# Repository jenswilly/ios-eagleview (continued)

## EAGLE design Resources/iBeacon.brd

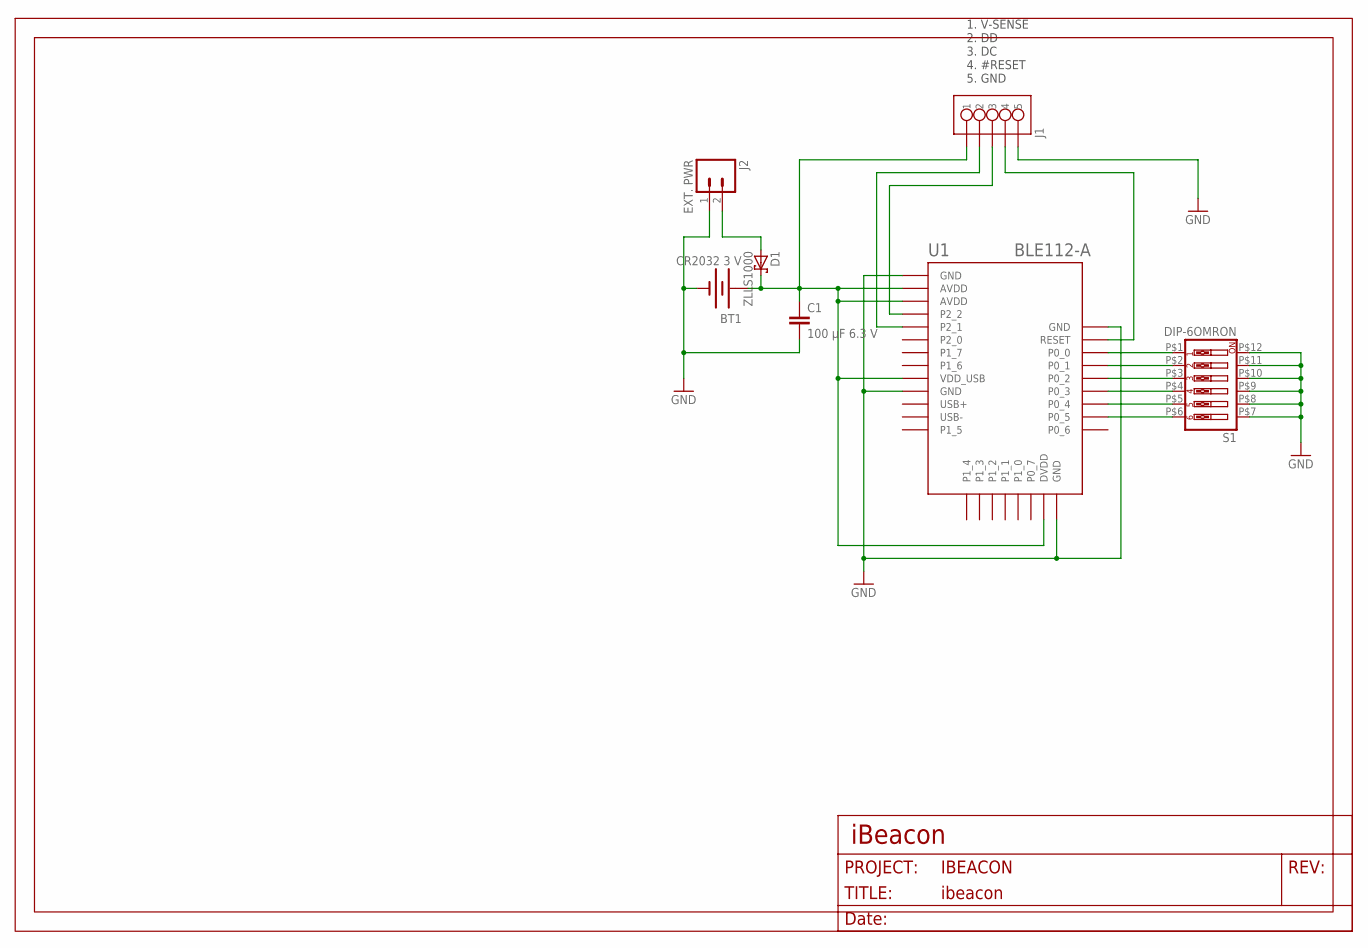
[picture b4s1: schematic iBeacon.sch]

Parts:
BT1: CR2032 3 V; BATTCON_20MM
C1: 100 µF 6.3 V; C1210K
D1: ZLLS1000; SOT23
IBEACON: iBeacon; DOCFIELD
J1: JST_SH_5
J2: EXT. PWR; 1X02
S1: DIP-6OMRON; OMRON_HALFPITCH_DIP_6
U1: BLE112-A; SF-BLUEGIGA_BLE112-A

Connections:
3V: BT1.1 (+), BT1.3 (+), C1.1, D1.3 (C), J1.P$1 (1), U1.AVDD1 (AVDD), U1.AVDD2 (AVDD), U1.DVDD, U1.VDD_USB
DC: J1.P$3 (3), U1.P2_2
DD: J1.P$2 (2), U1.P2_1
GND: BT1.2 (-), C1.2, J1.P$5 (5), J2.1, S1.P$7 (7), S1.P$8 (8), S1.P$9 (9), S1.P$10 (10), S1.P$11 (11), S1.P$12 (12), U1.GND1 (GND), U1.GND2 (GND), U1.GND3 (GND), U1.GND4 (GND)
unnamed: S1.P$1 (1), U1.P0_0
unnamed: S1.P$2 (2), U1.P0_1
unnamed: S1.P$3 (3), U1.P0_2
unnamed: S1.P$4 (4), U1.P0_3
unnamed: S1.P$5 (5), U1.P0_4
unnamed: S1.P$6 (6), U1.P0_5
unnamed: D1.1 (A), J2.2
RST: J1.P$4 (4), U1.RESET

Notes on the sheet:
1. V-SENSE 2. DD 3. DC 4. #RESET 5. GND

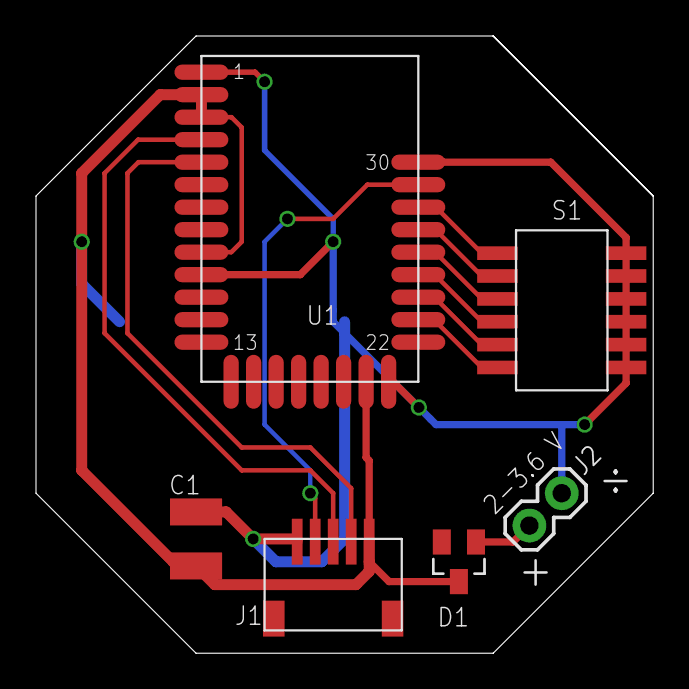
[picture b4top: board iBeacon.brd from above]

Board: 2 copper layers, 34.3 x 34.3 mm, 8 parts (1 on the bottom side), 12 nets.

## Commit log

2013-11-23 Submodules
2013-11-23 Added KissXML and work on schematic parsing.
2013-11-23 Work on drawing components
2013-11-25 More work on drawables
2013-11-25 Added EAGLE app icon
2013-11-25 Lots of work on drawing: Drawing all instances at their correct position now works
2013-11-25 Added nets and wires
2013-11-25 Showing values or deviceset name if no value + font size adjustment
2013-11-26 Smashed attributes
2013-11-26 Added busses
2013-11-26 Added net/bus labels
2013-11-26 Added junctions and multi-line texts
2013-11-26 Added circles
2013-11-27 Began work on arcs
2013-11-27 Got arcs working.
2013-11-28 Added to-do and iBeacon schematic.
2013-11-28 Added “middle” pin length + support for arcs in wires.
2013-11-28 Intrinsic content size + work on zoom/scroll.
2013-11-28 Relative zoom factor.
2013-11-28 Auto-centering of schematic view in scroll view (using auto-layout).
2013-11-28 Pinch zoom
2013-11-28 Cleanup.
2013-11-28 More cleanup.
2013-11-28 Added rectangle drawable
2013-11-28 Text rotations
2013-11-29 Implemented zoom to fit
2013-11-29 Began work on Dropbox loading
2013-11-29 Added dropbox framework
2013-12-03 Added minX and minY and corrected for negative origins
2013-12-03 Dropbox loading now uses MBProgressHUD and fixed sequence
2013-12-03 Animated zoom-to-fit + better Dropbox chooser nav. titles
2013-12-03 Fixed compiler warnings about [NSArray count] used as integer in printf + removed CouchbaseLite framework to avoid warning about missing arm64 architecture
2013-12-10 Implemented “Open in…” for sch files
2013-12-10 Added open schematic from zip archive feature.
2013-12-10 Improved zoom performance by using CATransform3D when zooming and only redrawing at end of pinch
2013-12-10 Zoom around pinch center
2013-12-10 Fix zoom-to-fit (cuts off lines); add padding
2013-12-17 Dropbox remembers last used folder when a file has been selected
2013-12-17 Removed DEBUG_LOGs
2013-12-26 Dropbox: Display .sch files in different style Dropbox: Disable selecting non-sch files
2013-12-26 Add icons to Dropbox chooser
2013-12-26 - Fixed re-picking documents - Removed DEBUG_LOGs
2013-12-26 Updated to-do
2013-12-26 - Fixed Dropbox chooser icon colors - Updated to-do
2014-01-08 Added error handling when opening schematic files from zip files
2014-01-19 Mirrored instances
2014-01-19 Added drawable: frame
2014-01-19 Placeholder texts for >DRAWING_NAME and >LAST_DATE_TIME
2014-01-24 Fixed frame placeholders + new icons for toolbar
2014-01-25 Work on detecting taps on instances
2014-01-26 Work on detail popup
2014-01-26 Added iPhone target
2014-01-26 New app icon
2014-01-26 Added Default-568h
2014-01-26 Added iPhone details popup
2014-01-26 Changed global tint color
2014-01-27 Fixed hit test for rotated/mirrored parts
2014-01-27 Refactored in preparation for support for board files.
2014-01-27 More refactoring in prep. for boards
2014-01-27 Basic board drawing
2014-01-27 Fixed hiding unused attributes for smashed symbols/packages
2014-01-28 Began work on layers
2014-01-28 Implemented pads; only draws elements in visible layers
2014-01-28 Use bottom layers for mirrored EAGLEElements on board files
2014-01-28 Fixed (int) warning; new provisioning profile; build no.
2014-01-29 Began work on drawable: smd
2014-01-29 Round corners on smd's
2014-01-29 Added signals to board files; added vias drawables
2014-01-29 Added layer colors + warning when a layer with an undefined color is used; improved calculation of intrinsic size; white/black backgrounds on view
2014-01-29 Adjusted positions/orientation for rotated attributes
2014-01-29 Hardcoded pins on layer 93
2014-01-29 Only loads active layers from files.
2014-01-29 Added library_name to EAGLEElements
2014-01-29 Shows details popup for elements on boards
2014-01-29 Work on mirrored rotations; fixed order of drawing board elements
2014-01-29 Added layers chooser to iPhone
2014-01-29 Sets white/black background on scroll view when opening board/schematic
2014-01-29 Build no.
2014-01-30 Auto diameter for pads; added limitations doc.
2014-01-30 Fixed layers list (checkmarks)
2014-01-30 Began work on fill patterns
2014-01-31 Added SR90 rotation; only selects attributes where not display = "off"
2014-01-31 Parses signal polygons (drawing disabled until overlap/fill can be fixed); added Thermometer board file
2014-01-31 Now sets background color on entire view; sets status bar color based on type of file
2014-02-01 Part popup is now a popover from the component on iPad only
2014-02-01 Add show/hide top/bottom layers from layers chooser view controller
2014-02-04 Fullscreen mode for iPhone
2014-02-04 Fixed arc drawing; fixed text rotation for compound rotations; now ignores description elements; build no.
2014-02-04 Changed hardcoded layer number for pins
2014-02-04 Parses initial layer visibility from file
2014-02-04 Added drawable: hole; refactored abstraction error to #define
2014-02-04 Refactored: moved layer parsing to EAGLEFile
2014-02-04 Refactored: moved library parsing to EAGLEFile
2014-02-04 Began work on layer drawing; refactored EAGLESchemativView -> EAGLEFileView
2014-02-04 Continued work on layer drawing
2014-02-05 Changed layered drawing; now uses tiled layers to prevent memory issues; caches instance symbol, library etc. for better performance
2014-02-05 More work on tiled drawing; added file name label
2014-02-07 Remembers last used Dropbox folder in user defaults
2014-02-07 Work work on fill patterns: implemented patterns 10 and 4
2014-02-07 Began work on finding components
2014-02-10 Fixed MR270 rotations for texts; fixed problem with non-attribute texts not being drawn
2014-02-18 Added "keep alive" setting
2014-02-18 Work on component searching
2014-02-20 Fixed layers popup orientation on iPhone
2014-03-19 Work on search/highlighted parts
2014-03-19 Fix for rotated and flipped objects and their bounding box
2014-03-19 Now opens .brd files as well; can choose which file in a zip archive to open
2014-12-01 Added Energy Shield board and schematic test files:
    - there are still issues with this file
2014-12-01 Added R35 and R30 rotations
2014-12-01 Added support for opening zip files where the .brd/.sch files are located in subfolders:
    - now all unzipped folders are recursively scanned for .brd and .sch files.
2014-12-01 Fixed issue that showed wrong values for reused symbols:
    - if several instances used the same symbol, the name and value texts might get reused also. Now textsForPlaceholders are located at instance level and set on the symbol in -[EAGLEInstance drawInCont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
2014-12-01 Now opens Energy Shield.sch on startup
2014-12-01 Searching in schematics:
    - added searching in schematics
2014-12-10 Fixed clean of temporary files after opening a zip archive.
2015-01-17 Began work on multiple modules and sheets:
    - added EAGLEModule and EAGLESheet classes
    - schematics now have .modules and .currentModuleIndex property and activeModule method
    - modules have .sheets and .activeSheet properties
2015-01-17 Now updates name label when switching module:
    - still only temporary code, mind you
2015-01-17 Began implementation of EAGLEDrawableModuleInstance:
    - still missing ports!
2015-01-18 Added EAGLEModulePort class
2015-01-18 Continued work on drawing module instances:
    - temporary drawing of ports
    - still missing correct symbol and port label
2015-01-18 Implemented hit-test and detail popup for module instances
2015-01-18 Work on drawing module instances:
    - ports are now drawn with a simple line regardless of port direction
    - port labels are drawn
    - renamed EAGLEModulePort to EAGLEDrawableModulePort
2015-01-19 Dropbox: updated API + added unlink + fixed loading from saved path + lazy loading of content in parent paths
2015-01-19 Zoom-to-fit on launch from built-in file + updated to-do
2015-01-19 Configured for Enterprise builds
2015-01-19 Implemented module picker
2015-01-19 Now also searches in value texts
2015-01-19 Added space between search/sheets/layers buttons on iPad
2015-01-19 Updated to deployment target iOS 8 + fixed deprecations:
    - fixed search to not use searchDisplayController
    - added launch screen XIB so UI looks ok on iPhone 6 too
    - updated to-do
    - removed some commented-out code
2015-01-19 Fixed hiding of document chooser view controller on iPhone
2015-01-22 Implemented double-tap on module instance to show module:
    - updated to-do
2015-01-22 New Dropbox and zoom-to-fit icons
2015-01-22 Placeholder view when no schematic/board is selected,
2015-01-22 Fixed issues re placeholder image:
    - fixed fullscreen (hide/show toolbar)
    - disabled fullscreen with placeholder image is visible
2015-01-25 Automatically attempts to open last used file.
2015-01-25 Fix part info popup location on iPhone
2015-01-25 Disable sheets picker if there is only one sheet/module or if it's a board file
2015-01-25 Added build script to set build number to number of git commits when archiving
2015-01-26 Fixed initial file loading + initial state of toolbar buttons
2015-01-26 Fixed layout warnings
2015-01-26 Hit-test: ignore components on top/bottom if relevant layer not shown
2015-01-27 Removed ios-library submodule
2015-01-27 Added ios-library as non-submodule files
2015-01-27 Removed unused files from ios-library
2015-01-27 Removed superflous schematic/board files + fixed warning re unused variable
2015-01-27 Added readme file
2015-01-31 Added Crashlytics framework:
    - Crashlytics added only for the Enterprise build scheme.
2015-02-08 Fixes #1: <pin> without length
2015-02-08 Housekeeping:
    - fixed linker warning
    - updated to-do
2015-02-08 Temporary handling of #4:
    - doesn't handle it spun elements correctly, but doesn't crash.
2015-02-08 Fixes #3: frame part when no file is loaded
2015-02-08 Housekeeping:
    - updated to-do
2015-02-08 Fixed #5: opening zip requires app to be active:
    - the zip file was attempted unzipped both from application:didFinishLaunchingWithOptions: _and_ from handleOpenURL:
2015-02-08 Build no. + to-do
